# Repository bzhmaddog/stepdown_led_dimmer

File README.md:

# Led dimmer using a stepdown converter module
A simple PCB to adjust brightness of led(s) using a Stepdown converter board and two resistors

# Application
For Pinball machine mods requiring a basic (fixed) lighting

# Release Notes
- v1.0 : Initial Release

# BOM
|Ref|Designation   | Description   | Qty   |Source  |
|---|---|---|---|---|
|U1|Stepdown converter|DC-DC converter| 1|https://fr.aliexpress.com/item/32880983608.html|
|J3|4 pins straight header| 2.54mm|1|   |
|J1,J2|2 pins bornier connector|Terminal block 5.08mm|2|   |
|R1|Resistor|-|1|  |
|RV1|Potentiometer|Vertical 3 pins|1|  |

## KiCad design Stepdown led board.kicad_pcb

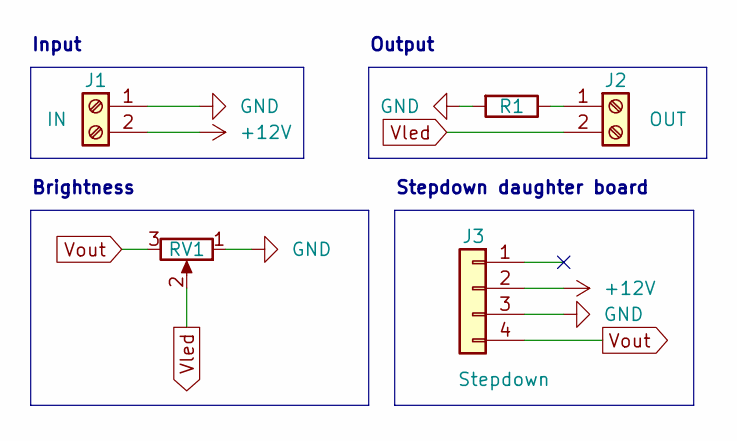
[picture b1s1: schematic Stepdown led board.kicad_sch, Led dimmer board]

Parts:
J1: IN; TerminalBlock_bornier-2_P5.08mm
J2: OUT; TerminalBlock_bornier-2_P5.08mm
J3: Stepdown; PinHeader_1x04_P2.54mm_Vertical
R1: R; R_2816_7142Metric_Pad3.20x4.45mm_HandSolder
RV1: Pot; Potentiometer_ACP_CA6-VSMD_Vertical

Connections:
+12V: J1.2, J3.2
GND: J1.1, J3.3, R1.2, RV1.1
unnamed: J2.1, R1.1
Vled: J2.2, RV1.2
Vout: J3.4, RV1.3

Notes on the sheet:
Output
Stepdown daughter board
Brightness
Input

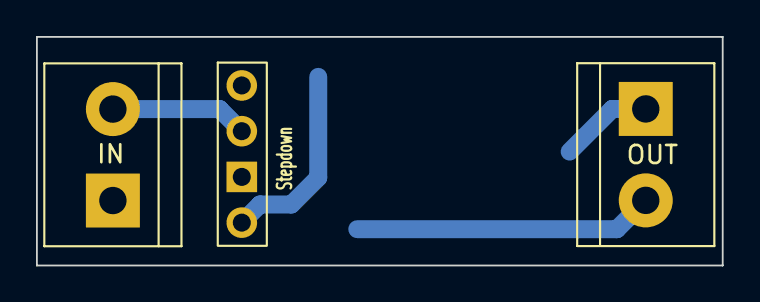
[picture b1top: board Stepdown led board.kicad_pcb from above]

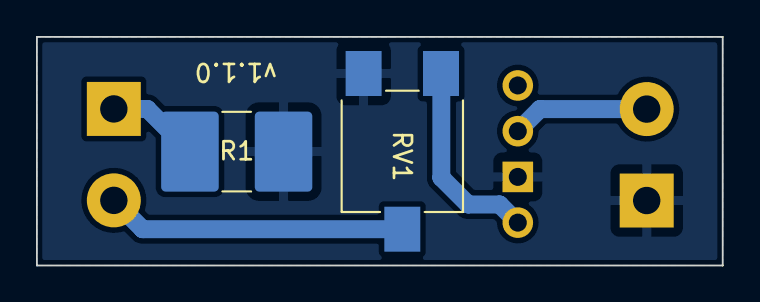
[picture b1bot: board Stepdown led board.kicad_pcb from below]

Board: 2 copper layers, 38.1 x 12.7 mm, 5 parts (2 on the bottom side), 5 nets.

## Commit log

2022-08-10 Initial Commit （v1.0)
2022-08-10 - Updated README.md with release note for v1.0
2022-08-10 - v1.1 (shorter version with component on both sides (WIP) - Reorganized production files folders
2022-08-21 - Fixed dumb stepdown module inversion - Fixed Front silkscreen
2022-08-25 Version 1.1.0 WIP
2022-08-25 - Schematic cleanup - Layout (silk) update
2022-08-28 Added solutions from DeepPCB.ai (not planning to use them anyway)
